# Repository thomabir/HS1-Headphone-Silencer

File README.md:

# HS1-Headphone-Silencer
A very basic small PCB to reduce the volume of wired headphones.

## Operating principle
A 10:1 voltage divider, realized with 10 Ohm and 1 Ohm resistors, reduces the voltage of the input by a factor of 10. Two copies of the circuit serve the two stereo channels. The source and the headphones can be connected via two 3.5 mm audio jacks.

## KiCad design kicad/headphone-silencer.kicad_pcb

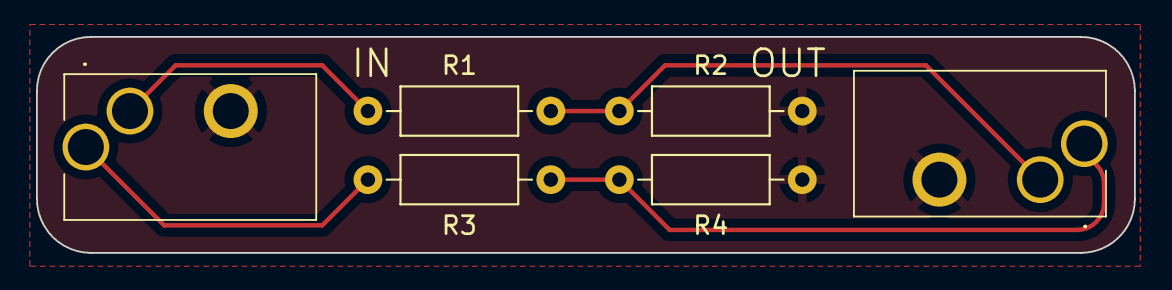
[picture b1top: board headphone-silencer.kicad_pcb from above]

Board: 2 copper layers, 61.0 x 12.0 mm, 6 parts (0 on the bottom side), 5 nets.

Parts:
J1, J2: AudioJack3; Kycon STX-3150-3C-1
R1, R2, R3, R4: R; R_Axial_DIN0207_L6.3mm_D2.5mm_P10.16mm_Horizontal

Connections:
GND: J1.1, J2.1, R2.2, R4.2
unnamed: J1.2, R1.1
unnamed: J1.4, R3.1
unnamed: J2.2, R1.2, R2.1
unnamed: J2.4, R3.2, R4.1

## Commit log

2024-01-19 Add pdfs
2024-01-19 Add LICENSE
2024-01-31 Add simplified schematic to Readme
